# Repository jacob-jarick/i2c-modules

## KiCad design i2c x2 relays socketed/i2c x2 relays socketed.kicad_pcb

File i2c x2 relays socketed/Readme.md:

== About ==

This is a i2c controlled relay module.

Featuring
* galvanic Isolated Power
* optical isolation for relay signals.
* i2c address dip switch
* indicator LEDs

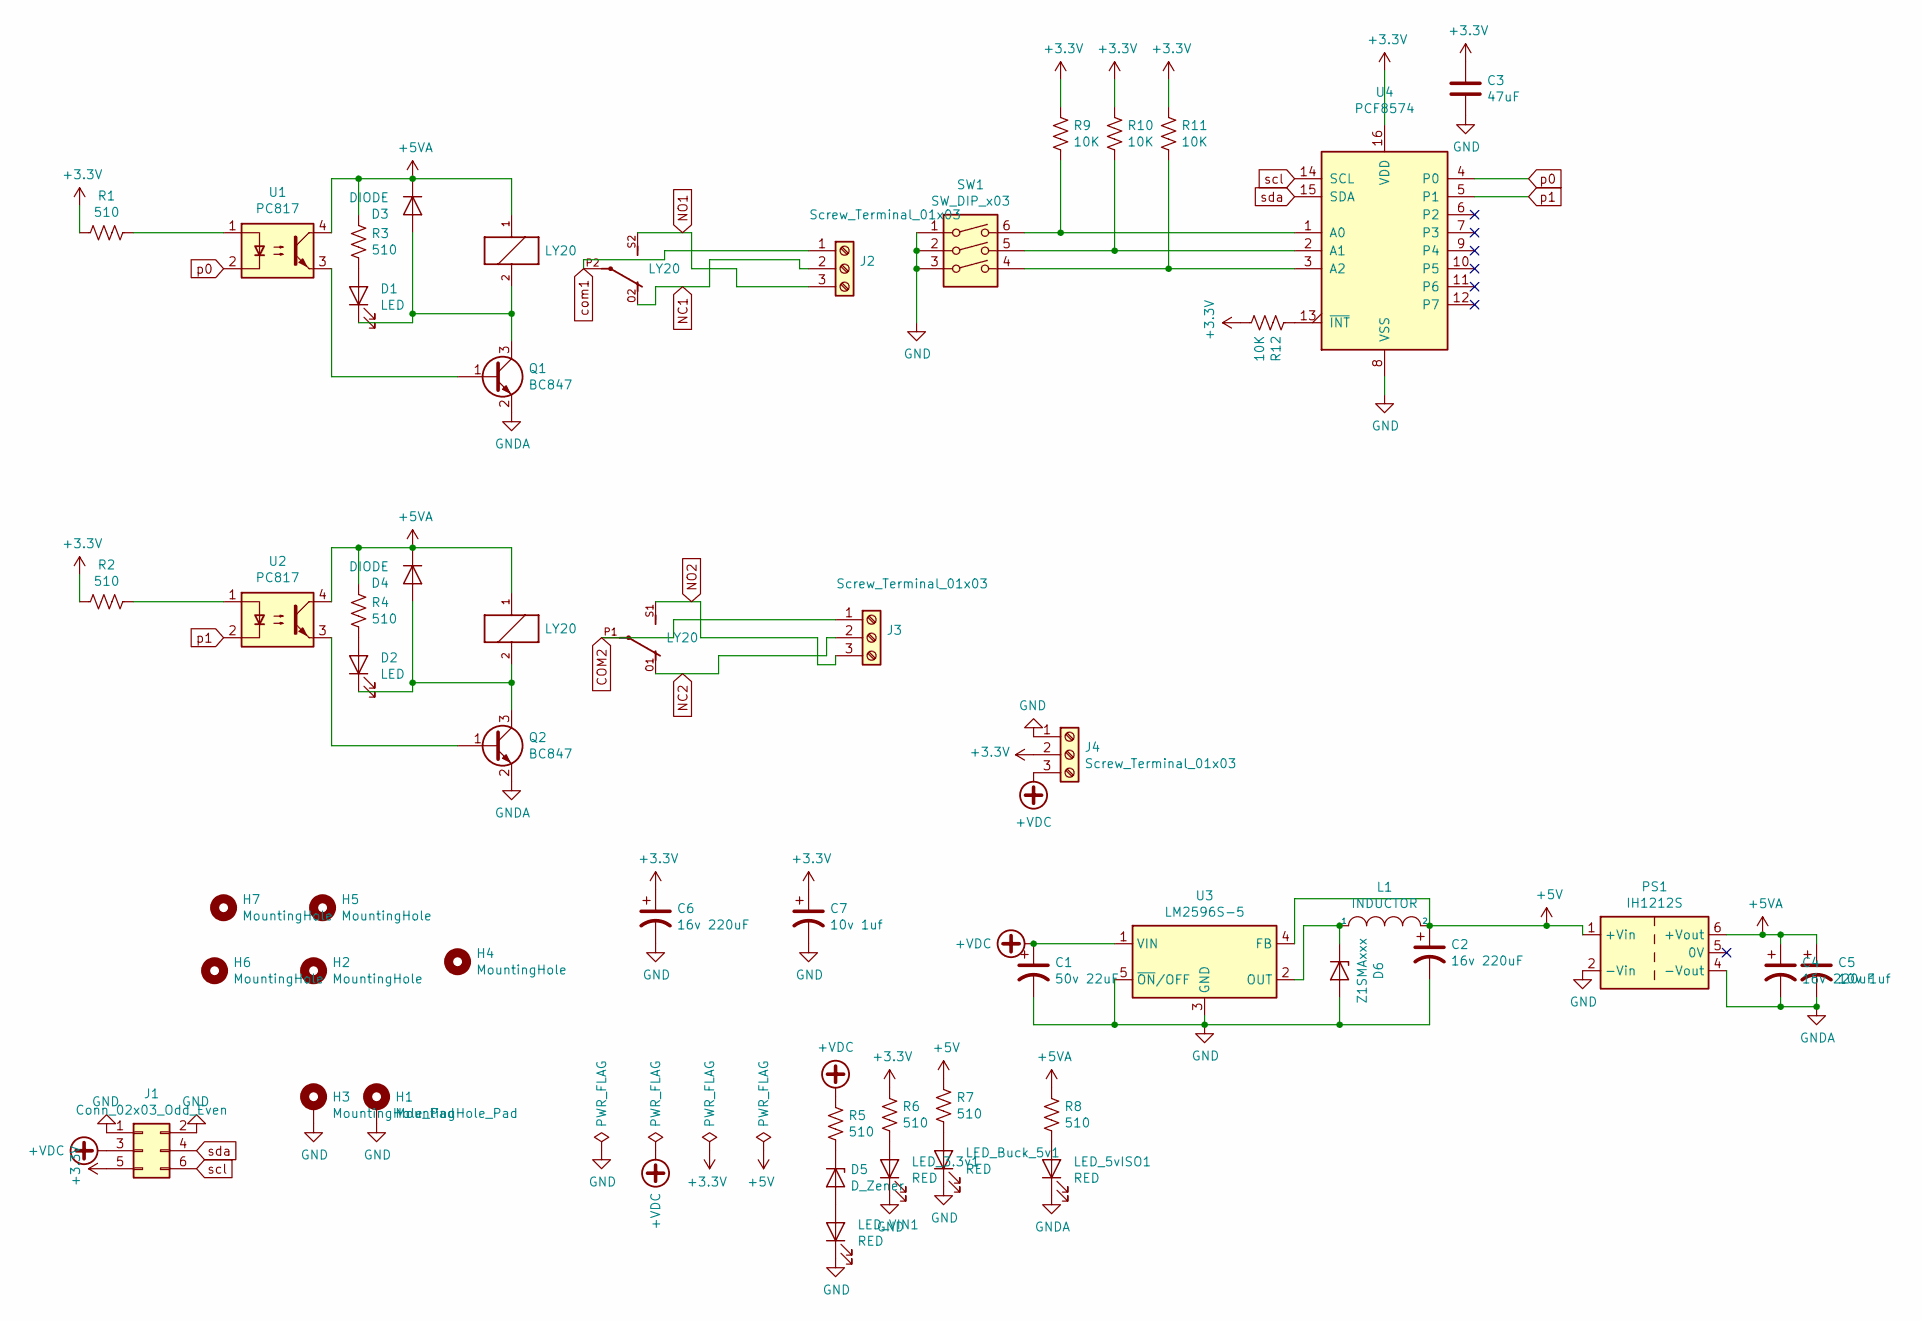
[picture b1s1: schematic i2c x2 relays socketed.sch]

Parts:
C1: 50v 22uF; CP_Radial_D8.0mm_P5.00mm
C2, C4, C6: 16v 220uF; CP_Radial_D8.0mm_P5.00mm
C3: 47uF; C_0805_2012Metric_Pad1.15x1.40mm_HandSolder
C5, C7: 10v 1uf; C_0805_2012Metric_Pad1.15x1.40mm_HandSolder
D1, D2: LED; LED_1206_3216Metric-witharrow
D3, D4: DIODE; D_SMA_Handsoldering
D5: D_Zener; D_SOD-323F-witharrow
D6: Z1SMAxxx; D_SMA_Handsoldering
H1, H3: MountingHole_Pad; MountingHole_4.3mm_M4_Pad_Via
H2, H4, H5, H6, H7: MountingHole; MountingHole_4.3mm_M4
J1: Conn_02x03_Odd_Even; IDC-Header_2x03_P2.54mm_Vertical
J2, J3: Screw_Terminal_01x03; PhoenixContact_MCV_1,5_3-G-5.08_1x03_P5.08mm_Vertical
J4: Screw_Terminal_01x03; PhoenixContact_MCV_1,5_3-G-3.81_1x03_P3.81mm_Vertical
K1, K2: LY20
L1: INDUCTOR; L_Taiyo-Yuden_NR-50xx_HandSoldering
LED_3.3v1, LED_5vISO1: RED; LED_1206_3216Metric-witharrow
LED_Buck_5v1: RED; LED_1206_3216Metric-witharrow
LED_VIN1: RED; LED_1206_3216Metric-witharrow
PS1: IH1212S; Converter_DCDC_XP_POWER-IHxxxxS_THT
Q1, Q2: BC847; SOT-23
R1, R2, R3, R4, R5, R6, R7, R8: 510; R_0805_2012Metric_Pad1.15x1.40mm_HandSolder
R9, R10, R11, R12: 10K; R_0805_2012Metric_Pad1.15x1.40mm_HandSolder
SW1: SW_DIP_x03; SW_DIP_SPSTx03_Slide_9.78x9.8mm_W7.62mm_P2.54mm
U1, U2: PC817
U3: LM2596S-5; TO-263-5_TabPin3
U4: PCF8574; SOIC-16W_7.5x10.3mm_P1.27mm

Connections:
+3V3: C3.1, C6.1, C7.1, J1.5, J4.2, R1.2, R2.2, R6.1, R9.1, R10.1, R11.1, R12.2, U4.16 (VDD)
+5V: C2.1, L1.2, PS1.1 (+Vin), R7.1, U3.4 (FB)
+5VA: C4.1, C5.1, D3.1 (K), D4.1 (K), K1.1, K2.1, PS1.6 (+Vout), R3.1, R4.1, R8.1, U1.4, U2.4
+VDC: C1.1, J1.3, J4.3, R5.1, U3.1 (VIN)
COM2: J3.1, K2.P1
GND: C1.2, C2.2, C3.2, C6.2, C7.2, D6.2 (A), H1.1, H3.1, J1.1, J1.2, J4.1, LED_3.3v1.1 (K), LED_Buck_5v1.1 (K), LED_VIN1.1 (K), PS1.2 (-Vin), SW1.1, SW1.2, SW1.3, U3.3 (GND), U3.5 (~ON~/OFF), U4.8 (VSS)
GNDA: C4.2, C5.2, LED_5vISO1.1 (K), PS1.4 (-Vout), Q1.2 (E), Q2.2 (E)
NC1: J2.2, K1.O2 (O)
NC2: J3.2, K2.O1 (O)
NO1: J2.3, K1.S2 (S)
NO2: J3.3, K2.S1 (S)
unnamed: D1.1 (K), D3.2 (A), K1.2, Q1.3 (C)
unnamed: D1.2 (A), R3.2
unnamed: D2.1 (K), D4.2 (A), K2.2, Q2.3 (C)
unnamed: D2.2 (A), R4.2
unnamed: D5.1 (K), R5.2
unnamed: D5.2 (A), LED_VIN1.2 (A)
unnamed: D6.1 (K), L1.1, U3.2 (OUT)
unnamed: LED_3.3v1.2 (A), R6.2
unnamed: LED_5vISO1.2 (A), R8.2
unnamed: LED_Buck_5v1.2 (A), R7.2
unnamed: Q1.1 (B), U1.3
unnamed: Q2.1 (B), U2.3
unnamed: R1.1, U1.1
unnamed: R2.1, U2.1
unnamed: R9.2, SW1.6, U4.1 (A0)
unnamed: R10.2, SW1.5, U4.2 (A1)
unnamed: R11.2, SW1.4, U4.3 (A2)
unnamed: R12.1, U4.13 (~INT~)
com1: J2.1, K1.P2
p0: U1.2, U4.4 (P0)
p1: U2.2, U4.5 (P1)
scl: J1.6, U4.14 (SCL)
sda: J1.4, U4.15 (SDA)

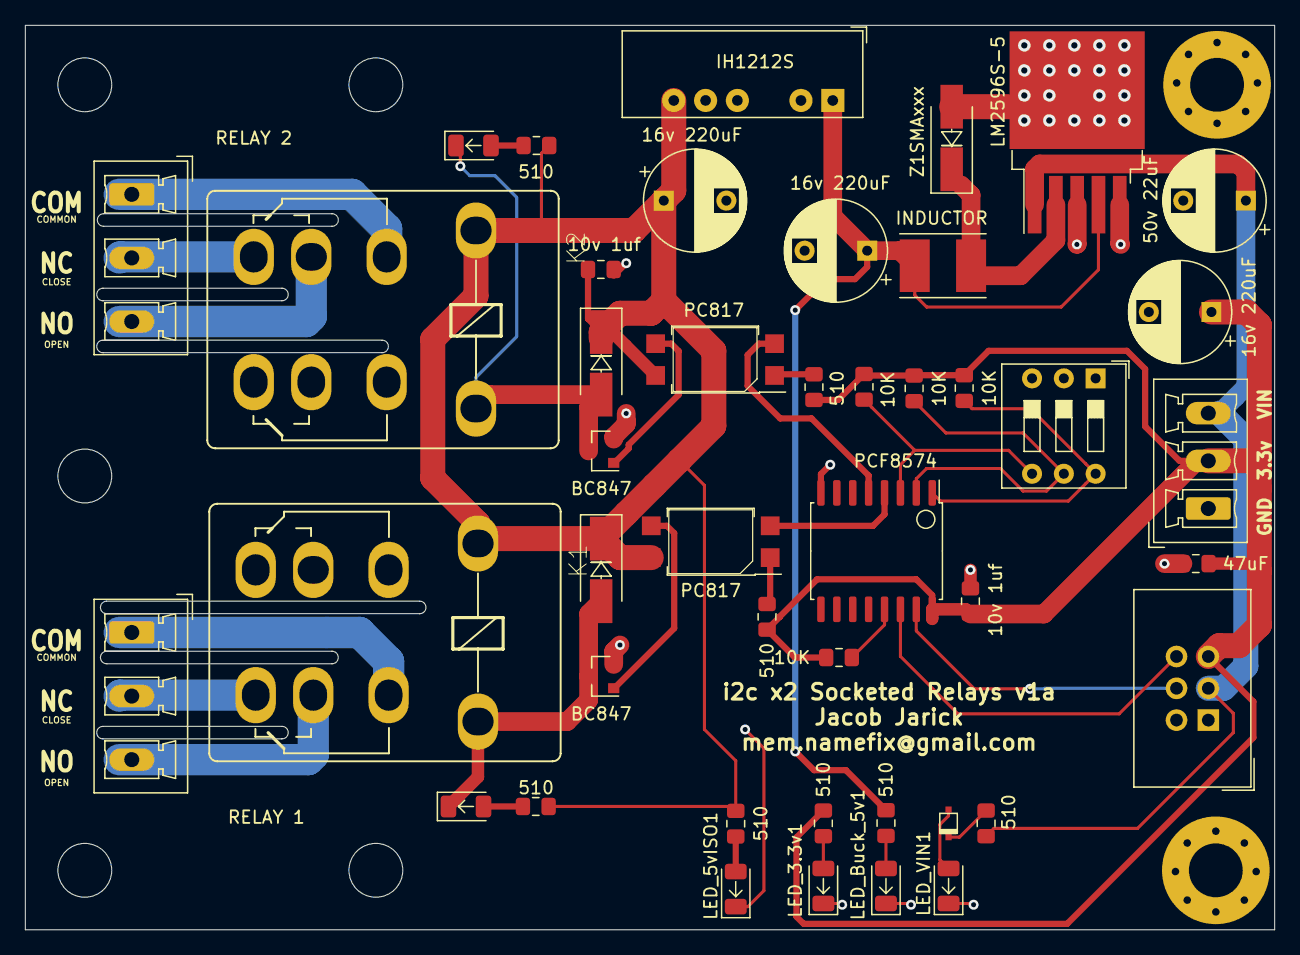
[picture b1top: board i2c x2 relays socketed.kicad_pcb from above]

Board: 2 copper layers, 99.8 x 72.2 mm, 51 parts (0 on the bottom side), 34 nets.

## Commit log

2019-11-25 vmon kicad files added
2020-01-19 i2c x2 relays socketed
